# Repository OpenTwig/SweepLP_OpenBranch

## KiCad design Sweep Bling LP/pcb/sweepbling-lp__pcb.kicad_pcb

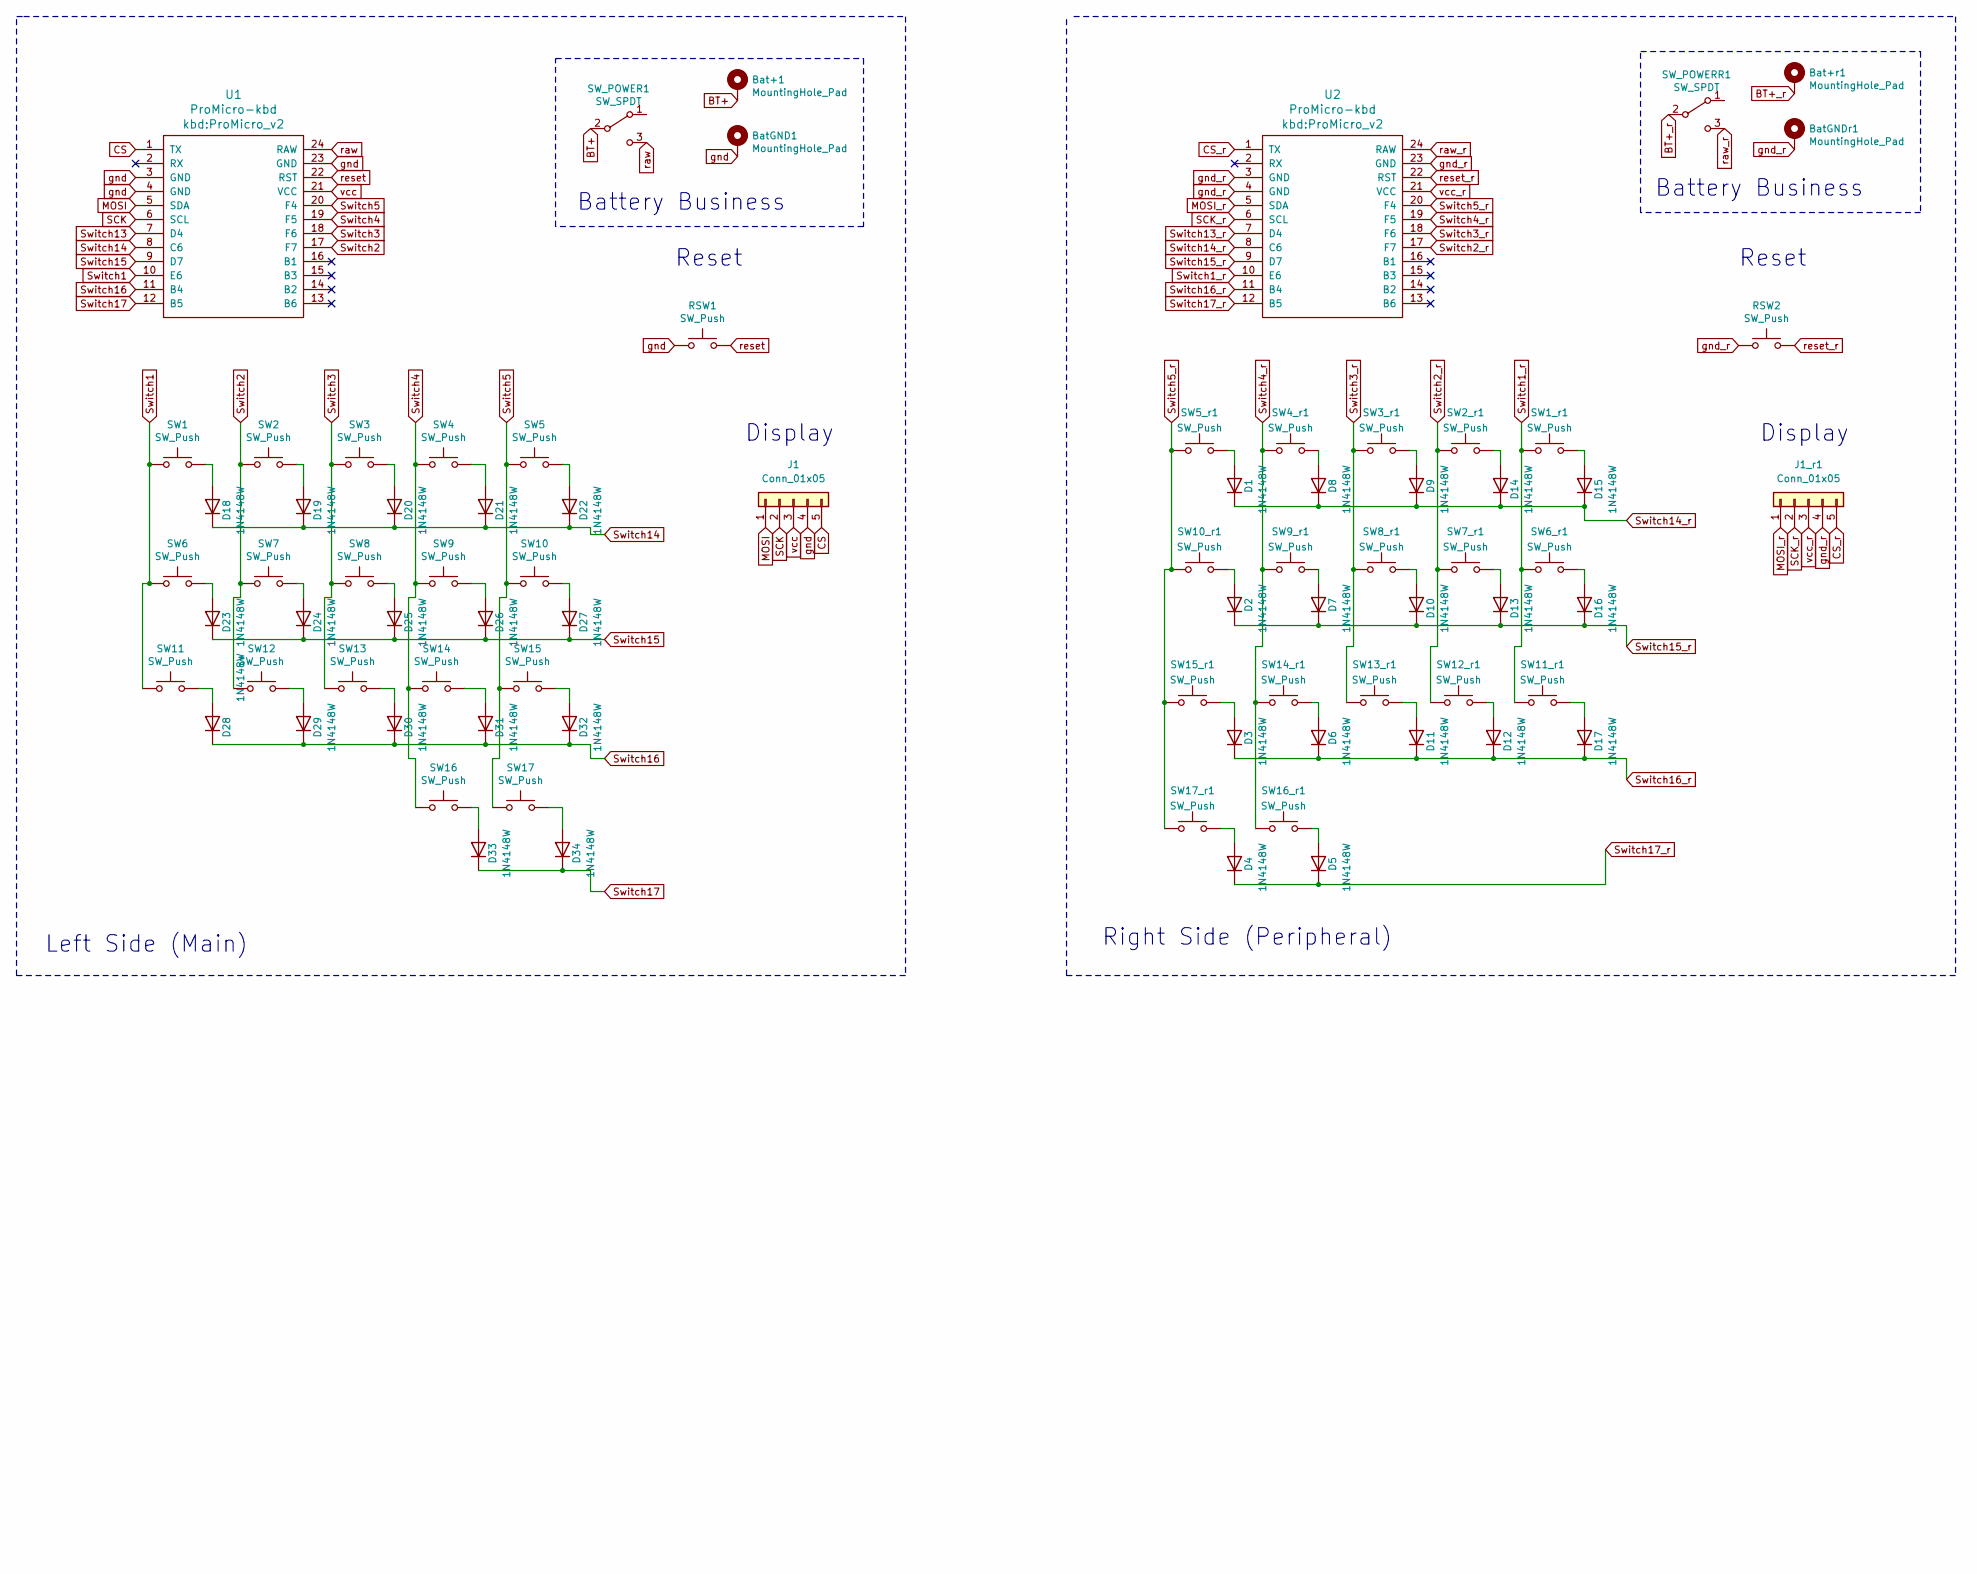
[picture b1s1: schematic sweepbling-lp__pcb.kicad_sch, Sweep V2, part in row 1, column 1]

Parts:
Bat+1: MountingHole_Pad; 1pin_conn
Bat+r1: MountingHole_Pad; 1pin_conn
BatGND1: MountingHole_Pad; 1pin_conn
BatGNDr1: MountingHole_Pad; 1pin_conn
D1, D2, D3, D4, D5, D6, D7, D8, D9, D10, D11, D12, D13, D14, D15, D16, D17, D18, D19, D20, D21, D22, D23, D24, D25, D26, D27, D28, D29, D30, D31, D32, D33, D34: 1N4148W; D_SOD-123
J1, J1_r1: Conn_01x05; PinSocket_1x05_P2.54mm_Vertical
RSW1, RSW2: SW_Push; ResetSW
SW1, SW1_r1, SW2, SW2_r1, SW3, SW3_r1, SW4, SW4_r1, SW5, SW5_r1, SW6, SW6_r1, SW7, SW7_r1, SW8, SW8_r1, SW9, SW9_r1, SW10, SW10_r1, SW11, SW11_r1, SW12, SW12_r1, SW13, SW13_r1, SW14, SW14_r1, SW15, SW15_r1, SW16, SW16_r1, SW17, SW17_r1: SW_Push; SW_PG1350_rev_DPB
SW_POWER1: SW_SPDT; SPDT_C128955
SW_POWERR1: SW_SPDT; SPDT_C128955
U1, U2: ProMicro-kbd; ProMicro_v2

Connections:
BT+: Bat+1.1, SW_POWER1.2 (B)
BT+_r: Bat+r1.1, SW_POWERR1.2 (B)
CS: J1.5, U1.1 (TX)
CS_r: J1_r1.5, U2.1 (TX)
MOSI: J1.1, U1.5 (SDA)
MOSI_r: J1_r1.1, U2.5 (SDA)
unnamed: D1.2 (A), SW5_r1.2
unnamed: D2.2 (A), SW10_r1.2
unnamed: D3.2 (A), SW15_r1.2
unnamed: D4.2 (A), SW17_r1.2
unnamed: D5.2 (A), SW16_r1.2
unnamed: D6.2 (A), SW14_r1.2
unnamed: D7.2 (A), SW9_r1.2
unnamed: D8.2 (A), SW4_r1.2
unnamed: D9.2 (A), SW3_r1.2
unnamed: D10.2 (A), SW8_r1.2
unnamed: D11.2 (A), SW13_r1.2
unnamed: D12.2 (A), SW12_r1.2
unnamed: D13.2 (A), SW7_r1.2
unnamed: D14.2 (A), SW2_r1.2
unnamed: D15.2 (A), SW1_r1.2
unnamed: D16.2 (A), SW6_r1.2
unnamed: D17.2 (A), SW11_r1.2
unnamed: D18.2 (A), SW1.2
unnamed: D19.2 (A), SW2.2
unnamed: D20.2 (A), SW3.2
unnamed: D21.2 (A), SW4.2
unnamed: D22.2 (A), SW5.2
unnamed: D23.2 (A), SW6.2
unnamed: D24.2 (A), SW7.2
unnamed: D25.2 (A), SW8.2
unnamed: D26.2 (A), SW9.2
unnamed: D27.2 (A), SW10.2
unnamed: D28.2 (A), SW11.2
unnamed: D29.2 (A), SW12.2
unnamed: D30.2 (A), SW13.2
unnamed: D31.2 (A), SW14.2
unnamed: D32.2 (A), SW15.2
unnamed: D33.2 (A), SW16.2
unnamed: D34.2 (A), SW17.2
SCK: J1.2, U1.6 (SCL)
SCK_r: J1_r1.2, U2.6 (SCL)
Switch1: SW1.1, SW6.1, SW11.1, U1.10 (E6)
Switch1_r: SW1_r1.1, SW6_r1.1, SW11_r1.1, U2.10 (E6)
Switch2: SW2.1, SW7.1, SW12.1, U1.17 (F7)
Switch2_r: SW2_r1.1, SW7_r1.1, SW12_r1.1, U2.17 (F7)
Switch3: SW3.1, SW8.1, SW13.1, U1.18 (F6)
Switch3_r: SW3_r1.1, SW8_r1.1, SW13_r1.1, U2.18 (F6)
Switch4: SW4.1, SW9.1, SW14.1, SW16.1, U1.19 (F5)
Switch4_r: SW4_r1.1, SW9_r1.1, SW14_r1.1, SW16_r1.1, U2.19 (F5)
Switch5: SW5.1, SW10.1, SW15.1, SW17.1, U1.20 (F4)
Switch5_r: SW5_r1.1, SW10_r1.1, SW15_r1.1, SW17_r1.1, U2.20 (F4)
Switch13: U1.7 (D4)
Switch13_r: U2.7 (D4)
Switch14: D18.1 (K), D19.1 (K), D20.1 (K), D21.1 (K), D22.1 (K), U1.8 (C6)
Switch14_r: D1.1 (K), D8.1 (K), D9.1 (K), D14.1 (K), D15.1 (K), U2.8 (C6)
Switch15: D23.1 (K), D24.1 (K), D25.1 (K), D26.1 (K), D27.1 (K), U1.9 (D7)
Switch15_r: D2.1 (K), D7.1 (K), D10.1 (K), D13.1 (K), D16.1 (K), U2.9 (D7)
Switch16: D28.1 (K), D29.1 (K), D30.1 (K), D31.1 (K), D32.1 (K), U1.11 (B4)
Switch16_r: D3.1 (K), D6.1 (K), D11.1 (K), D12.1 (K), D17.1 (K), U2.11 (B4)
Switch17: D33.1 (K), D34.1 (K), U1.12 (B5)
Switch17_r: D4.1 (K), D5.1 (K), U2.12 (B5)
gnd: BatGND1.1, J1.4, RSW1.1, U1.3 (GND), U1.4 (GND), U1.23 (GND)
gnd_r: BatGNDr1.1, J1_r1.4, RSW2.1, U2.3 (GND), U2.4 (GND), U2.23 (GND)
raw: SW_POWER1.3 (C), U1.24 (RAW)
raw_r: SW_POWERR1.3 (C), U2.24 (RAW)
reset: RSW1.2, U1.22 (RST)
reset_r: RSW2.2, U2.22 (RST)
vcc: J1.3, U1.21 (VCC)
vcc_r: J1_r1.3, U2.21 (VCC)

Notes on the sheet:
Battery Business
Reset
Left Side (Main)
Display
Right Side (Peripheral)

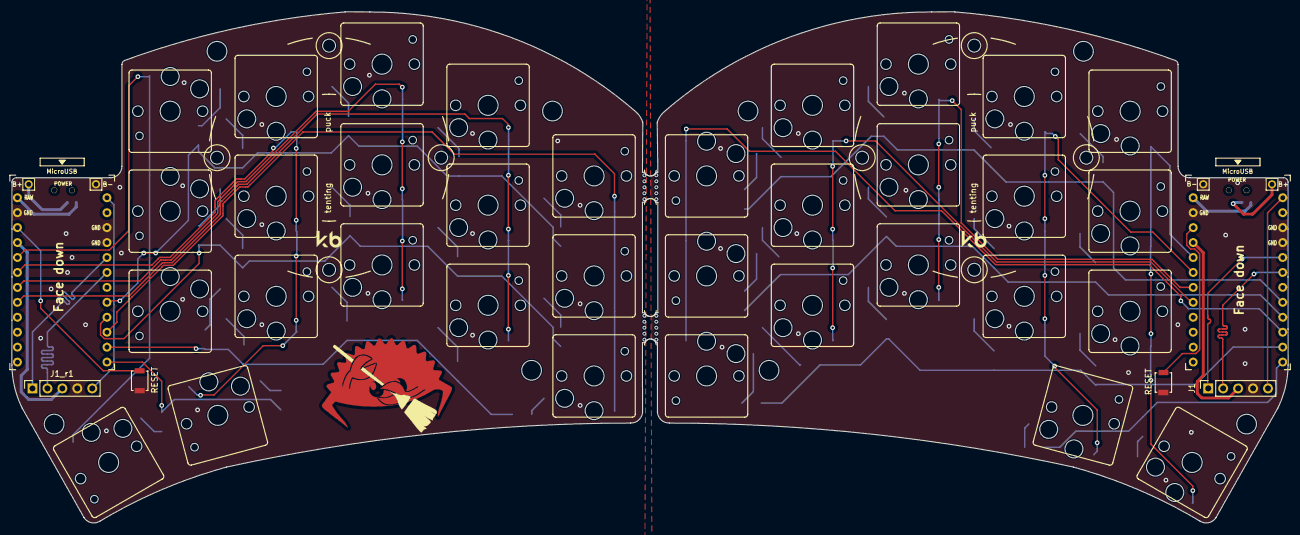
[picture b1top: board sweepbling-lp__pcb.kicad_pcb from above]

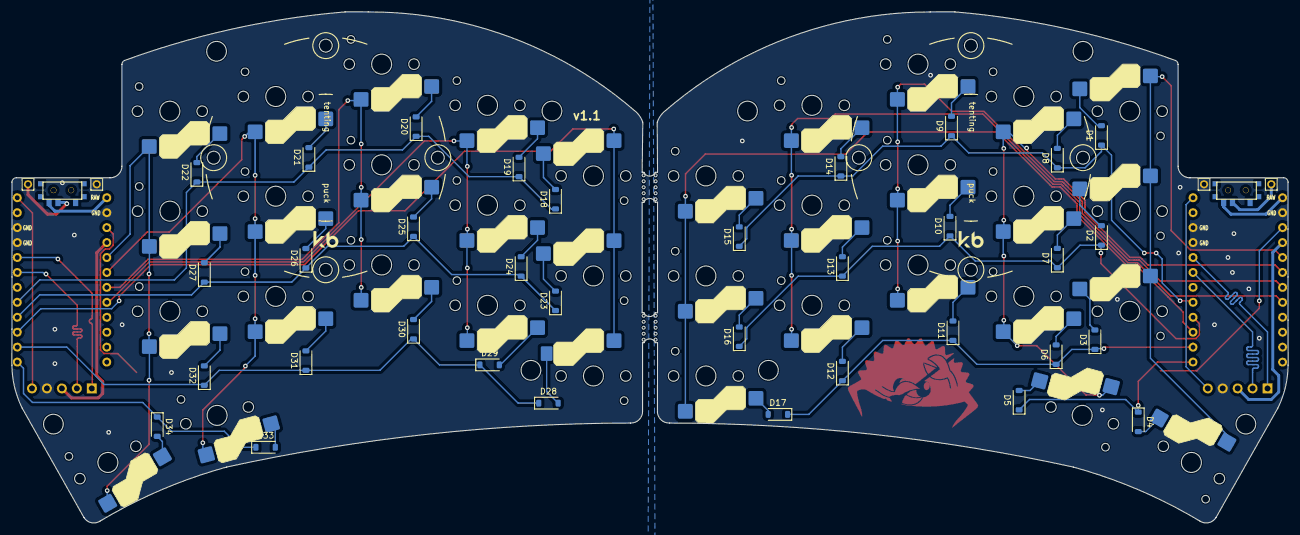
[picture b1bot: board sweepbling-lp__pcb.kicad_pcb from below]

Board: 2 copper layers, 216.9 x 86.9 mm, 85 parts (36 on the bottom side), 68 nets.

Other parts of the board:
REF_PUCK_R: Tenting Puck; Tenting_Puck2_no_pads
SweepLogo: LOGO; ferris_broom
e: Tenting Puck; Tenting_Puck2_no_pads
mouse-bite-2mm-slot1, mouse-bite-2mm-slot2: VAL**; mouse-bite-5mm-slot-with-space-for-track

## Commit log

2025-07-21 Add Bling-MX bottom.dxf
2025-08-27 edited Blink_LP
2025-08-28 traces addition
2025-08-28 traces
2025-09-09 final prod
